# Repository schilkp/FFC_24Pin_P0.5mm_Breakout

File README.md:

# 24 Pin 0.5mm Pitch FFC Breakout

A simple and breadboard-ready breakout.

Philipp Schilk, 2020

https://github.com/TheSchilk/FFC_24Pin_P0.5mm_Breakout

Should fit into any breadboard with the two pin-header rows. 

1 Layer

Connectors that should fit:

TE 2-1734839-4 ([Mouser.com](http://mouser.com/ProductDetail/TE-Connectivity-Buchanan/2-1734839-4?qs=Sm6ibA7evxgHWeCe9t1tOw==))
CKMTW  C132514 ([Lcsc.com](https://lcsc.com/product-detail/FFC-FPC-Connectors_Ckmtw-Shenzhen-Cankemeng-C132514_C132514.html))

And probably many others...

## JLCpcb Note:
When ordering these from JLCpcb (ready zip in releases), select
'2 Layer' instead of '1 Layer'. It is much cheaper. Also I am not sure you would get a pad
on both sides of the pin-header holes. 

(Do specify in the comments that there are no traces on the bottom layer, otherwise you
might get an email asking about that)

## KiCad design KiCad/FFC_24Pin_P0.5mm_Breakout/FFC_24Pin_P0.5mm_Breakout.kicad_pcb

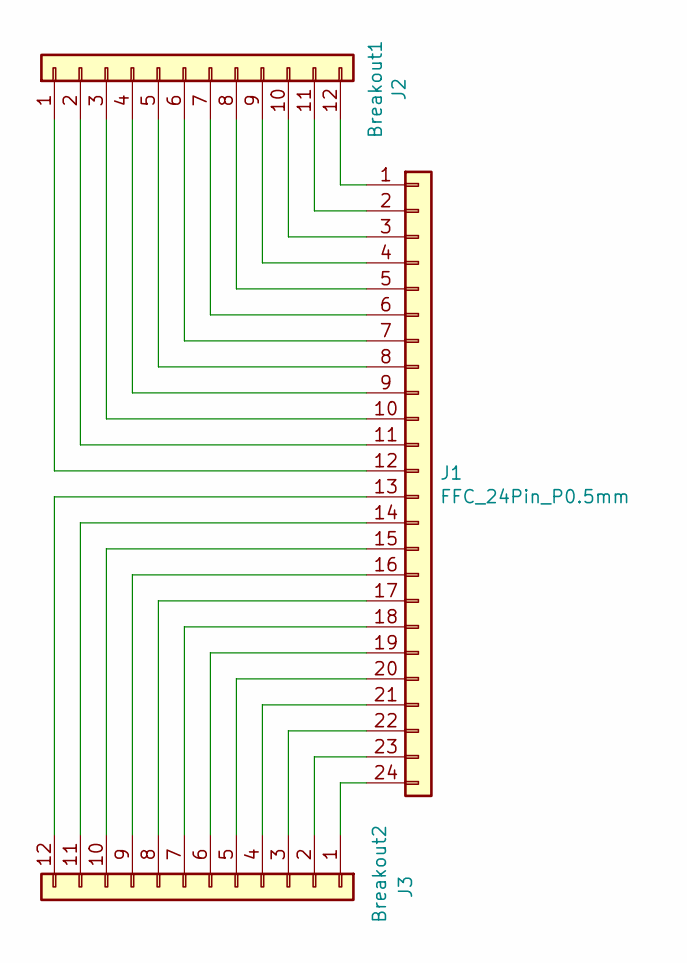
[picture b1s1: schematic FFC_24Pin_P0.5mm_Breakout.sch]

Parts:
J1: FFC_24Pin_P0.5mm; TE_2-1734839-4_1x24-1MP_P0.5mm_Horizontal
J2: Breakout1; PinHeader_1x12_P2.54mm_Vertical
J3: Breakout2; PinHeader_1x12_P2.54mm_Vertical

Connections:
unnamed: J1.1, J2.12
unnamed: J1.2, J2.11
unnamed: J1.3, J2.10
unnamed: J1.4, J2.9
unnamed: J1.5, J2.8
unnamed: J1.6, J2.7
unnamed: J1.7, J2.6
unnamed: J1.8, J2.5
unnamed: J1.9, J2.4
unnamed: J1.10, J2.3
unnamed: J1.11, J2.2
unnamed: J1.12, J2.1
unnamed: J1.13, J3.12
unnamed: J1.14, J3.11
unnamed: J1.15, J3.10
unnamed: J1.16, J3.9
unnamed: J1.17, J3.8
unnamed: J1.18, J3.7
unnamed: J1.19, J3.6
unnamed: J1.20, J3.5
unnamed: J1.21, J3.4
unnamed: J1.22, J3.3
unnamed: J1.23, J3.2
unnamed: J1.24, J3.1

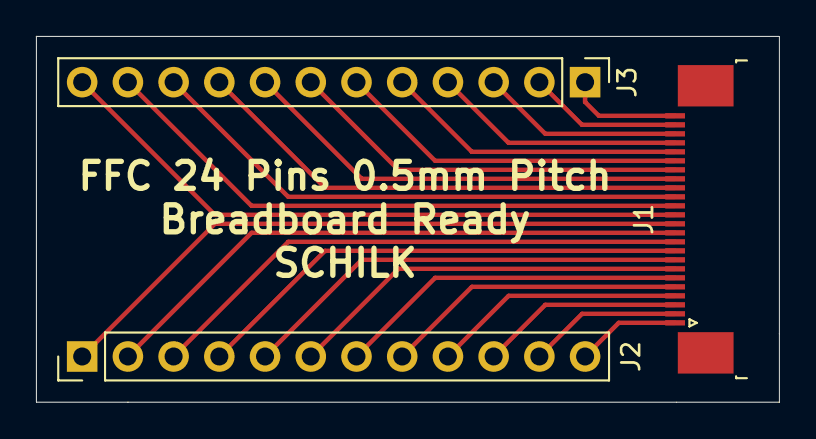
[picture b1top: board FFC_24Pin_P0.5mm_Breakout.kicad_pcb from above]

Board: 2 copper layers, 41.3 x 20.3 mm, 3 parts (0 on the bottom side), 24 nets.

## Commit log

2020-06-05 Added Breakout + Readme
2021-05-24 Added .gitattributes
